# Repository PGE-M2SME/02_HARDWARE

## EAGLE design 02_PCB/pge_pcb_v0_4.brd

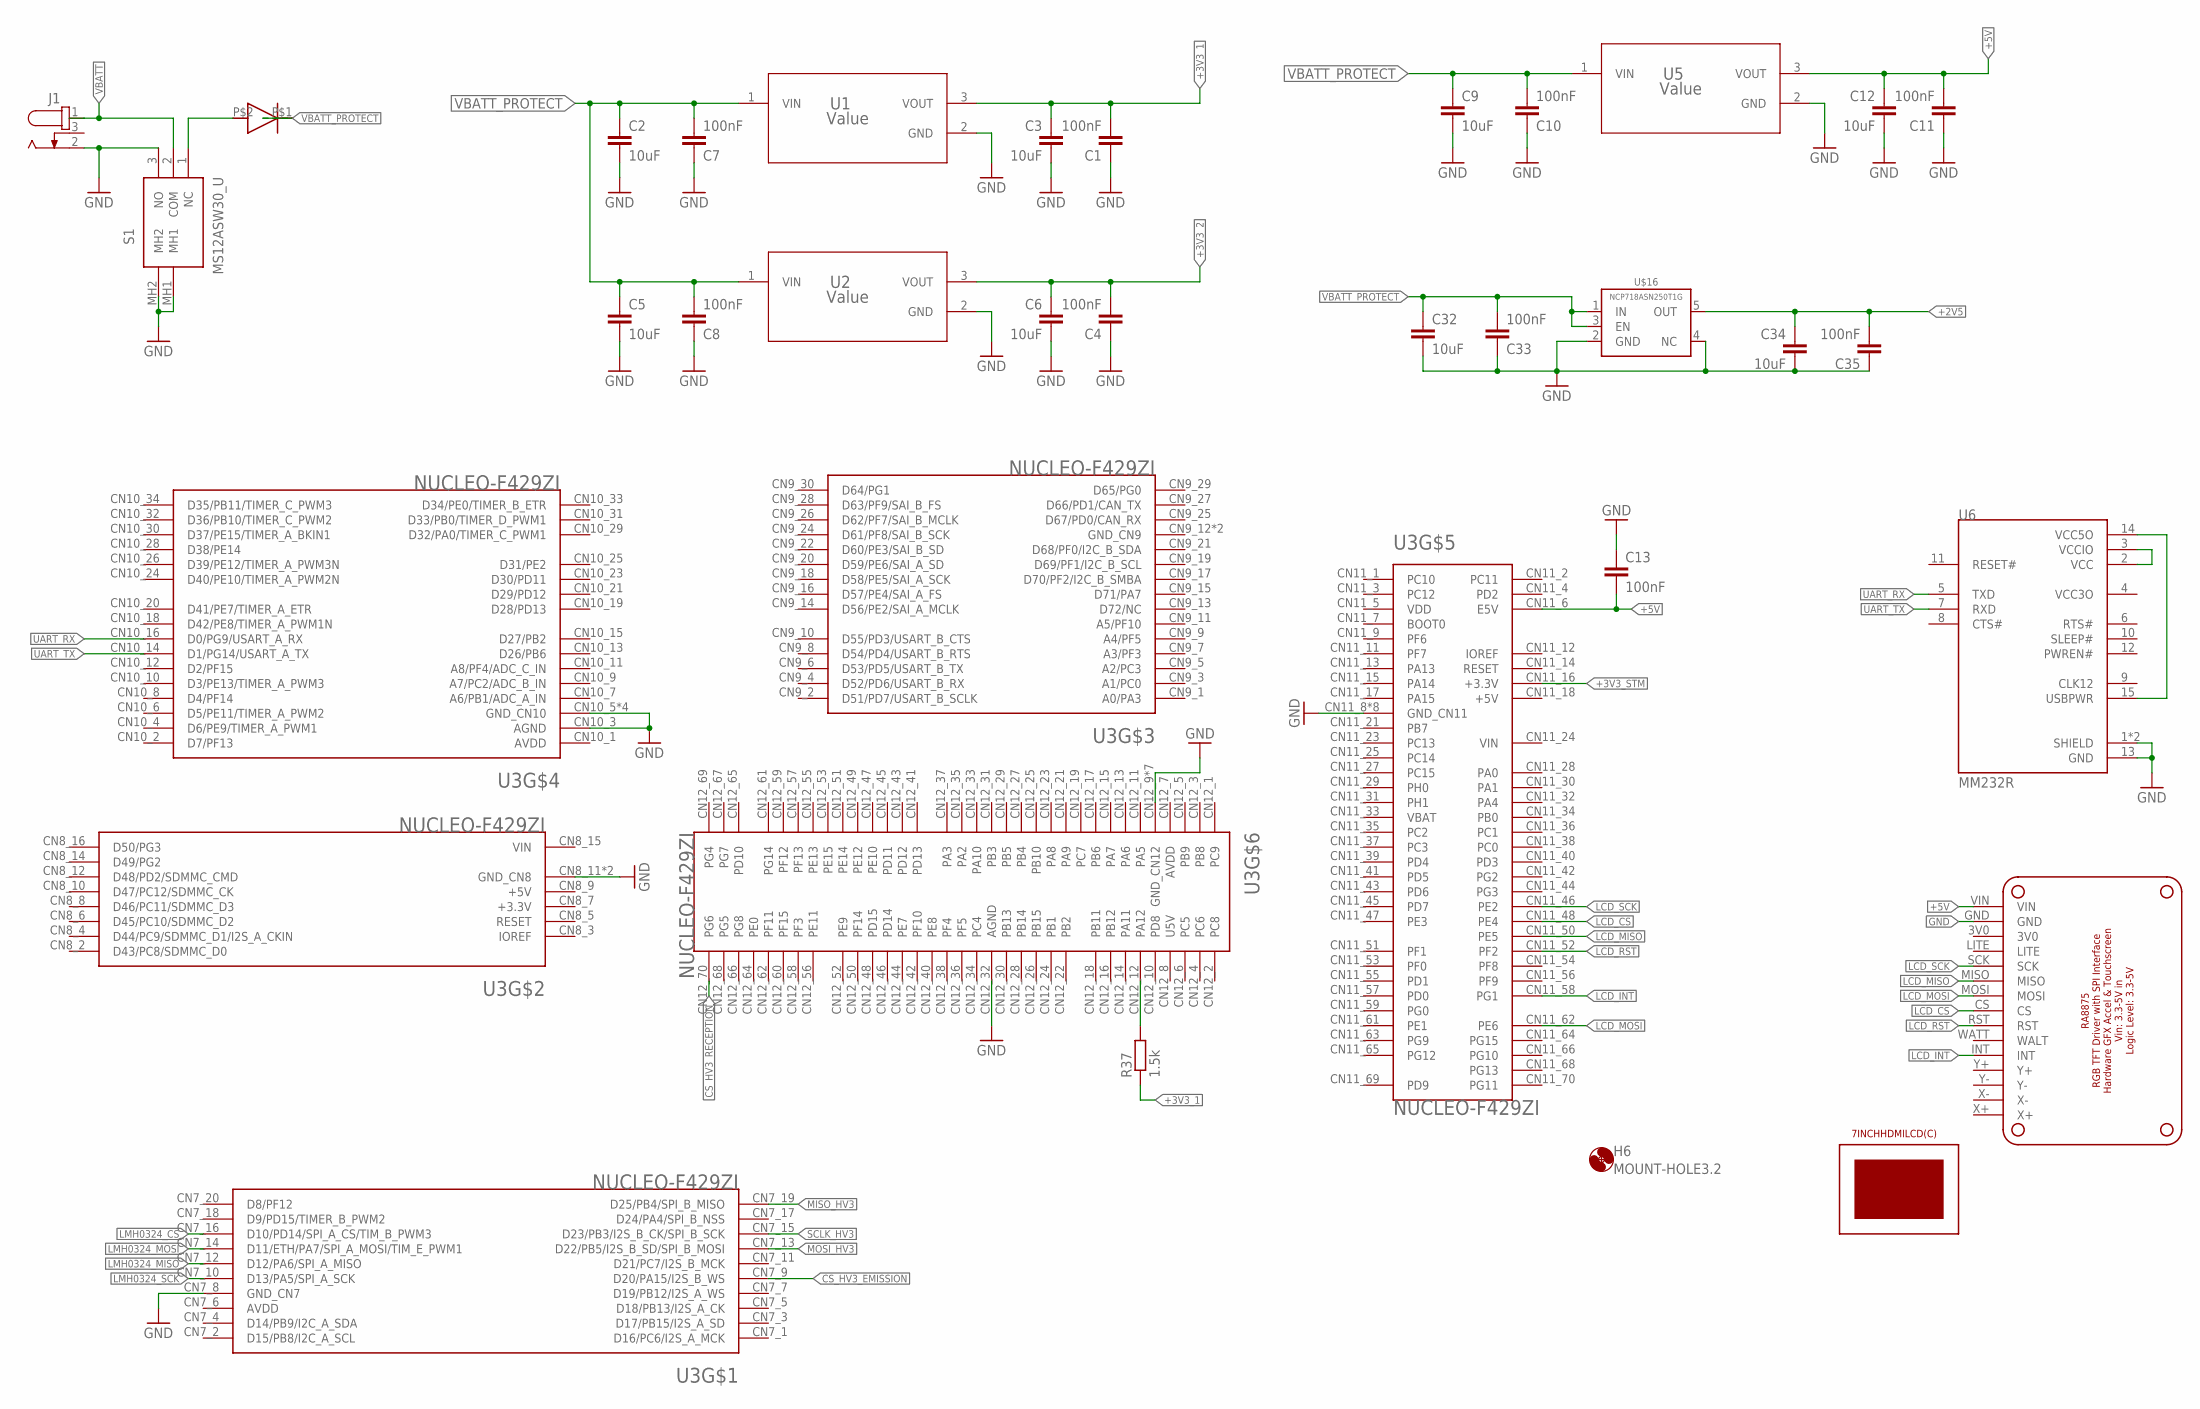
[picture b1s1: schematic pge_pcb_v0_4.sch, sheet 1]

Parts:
C1, C4, C7, C8, C10, C11, C13, C33, C35: 100nF; C0603
C2, C9, C32: 10uF; C0805
C3, C5, C6, C12, C34: 10uF; C0603
H6: MOUNT-HOLE3.2; 3,2
J1: 694106301002
R37: 1.5k; R0603
S1: MS12ASW30_U; MS12ASW30U
U1, U2, U5: Value; EAB0003A
U3: NUCLEO-F429ZI; MODULE_NUCLEO-F429ZI
U6: MM232R; FTDI_MM232R
U$1: V8PAL45HM3_A/I; DO-221BC(SMPA)
U$3: 7INCHHDMILCD(C)
U$15: RA8875_BOARD; RA88758_BOARD
U$16: NCP718ASN250T1G; SOT23-5

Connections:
+2V5: C34.1, C35.2, U$16.5 (OUT); also elsewhere on the board
+3V3_1: C1.2, C3.1, R37.1, U1.3 (VOUT); also elsewhere on the board
+3V3_2: C4.2, C6.1, U2.3 (VOUT); also elsewhere on the board
+3V3_STM: U3.CN11_16 (+3.3V)
+5V: C11.2, C12.1, C13.2, U3.CN11_6 (E5V), U5.3 (VOUT), U$15.VIN; also elsewhere on the board
CS_HV3_EMISSION: U3.CN7_9 (D20/PA15/I2S_B_WS); also elsewhere on the board
CS_HV3_RECEPTION: U3.CN12_70 (PG6); also elsewhere on the board
GND: C1.1, C2.2, C3.2, C4.1, C5.2, C6.2, C7.1, C8.1, C9.2, C10.1, C11.1, C12.2, C13.1, C32.2, C33.1, C34.2, C35.1, J1.2, S1.3 (NO), S1.MH1, S1.MH2, U1.2 (GND), U2.2 (GND), U3.CN7_8 (GND_CN7), U3.CN8_11 (GND_CN8), U3.CN8_13 (GND_CN8), U3.CN10_3 (AGND), U3.CN10_5 (GND_CN10), U3.CN10_17 (GND_CN10), U3.CN10_22 (GND_CN10), U3.CN10_27 (GND_CN10), U3.CN11_8 (GND_CN11), U3.CN11_19 (GND_CN11), U3.CN11_20 (GND_CN11), U3.CN11_22 (GND_CN11), U3.CN11_49 (GND_CN11), U3.CN11_60 (GND_CN11), U3.CN11_71 (GND_CN11), U3.CN11_72 (GND_CN11), U3.CN12_9 (GND_CN12), U3.CN12_20 (GND_CN12), U3.CN12_32 (AGND), U3.CN12_39 (GND_CN12), U3.CN12_54 (GND_CN12), U3.CN12_63 (GND_CN12), U3.CN12_71 (GND_CN12), U3.CN12_72 (GND_CN12), U5.2 (GND), U6.1 (SHIELD), U6.13 (GND), U6.16 (SHIELD), U$15.GND, U$16.2 (GND), U$16.4 (NC); also elsewhere on the board
LCD_CS: U3.CN11_48 (PE4), U$15.CS
LCD_INT: U3.CN11_58 (PG1), U$15.INT
LCD_MISO: U3.CN11_50 (PE5), U$15.MISO
LCD_MOSI: U3.CN11_62 (PE6), U$15.MOSI
LCD_RST: U3.CN11_52 (PF2), U$15.RST
LCD_SCK: U3.CN11_46 (PE2), U$15.SCK
LMH0324_CS: U3.CN7_16 (D10/PD14/SPI_A_CS/TIM_B_PWM3); also elsewhere on the board
LMH0324_MISO: U3.CN7_12 (D12/PA6/SPI_A_MISO); also elsewhere on the board
LMH0324_MOSI: U3.CN7_14 (D11/ETH/PA7/SPI_A_MOSI/TIM_E_PWM1); also elsewhere on the board
LMH0324_SCK: U3.CN7_10 (D13/PA5/SPI_A_SCK); also elsewhere on the board
MISO_HV3: U3.CN7_19 (D25/PB4/SPI_B_MISO); also elsewhere on the board
MOSI_HV3: U3.CN7_13 (D22/PB5/I2S_B_SD/SPI_B_MOSI); also elsewhere on the board
unnamed: S1.1 (NC), U$1.P$2 (ANODE)
unnamed: U6.2 (VCC), U6.3 (VCCIO)
unnamed: U6.14 (VCC5O), U6.15 (USBPWR)
unnamed: R37.2, U3.CN12_12 (PA12)
SCLK_HV3: U3.CN7_15 (D23/PB3/I2S_B_CK/SPI_B_SCK); also elsewhere on the board
UART_RX: U3.CN10_16 (D0/PG9/USART_A_RX), U6.5 (TXD)
UART_TX: U3.CN10_14 (D1/PG14/USART_A_TX), U6.7 (RXD)
VBATT: J1.1, S1.2 (COM)
VBATT_PROTECT: C2.1, C5.1, C7.2, C8.2, C9.1, C10.2, C32.1, C33.2, U1.1 (VIN), U2.1 (VIN), U5.1 (VIN), U$1.P$1 (CATHODE), U$16.1 (IN), U$16.3 (EN)

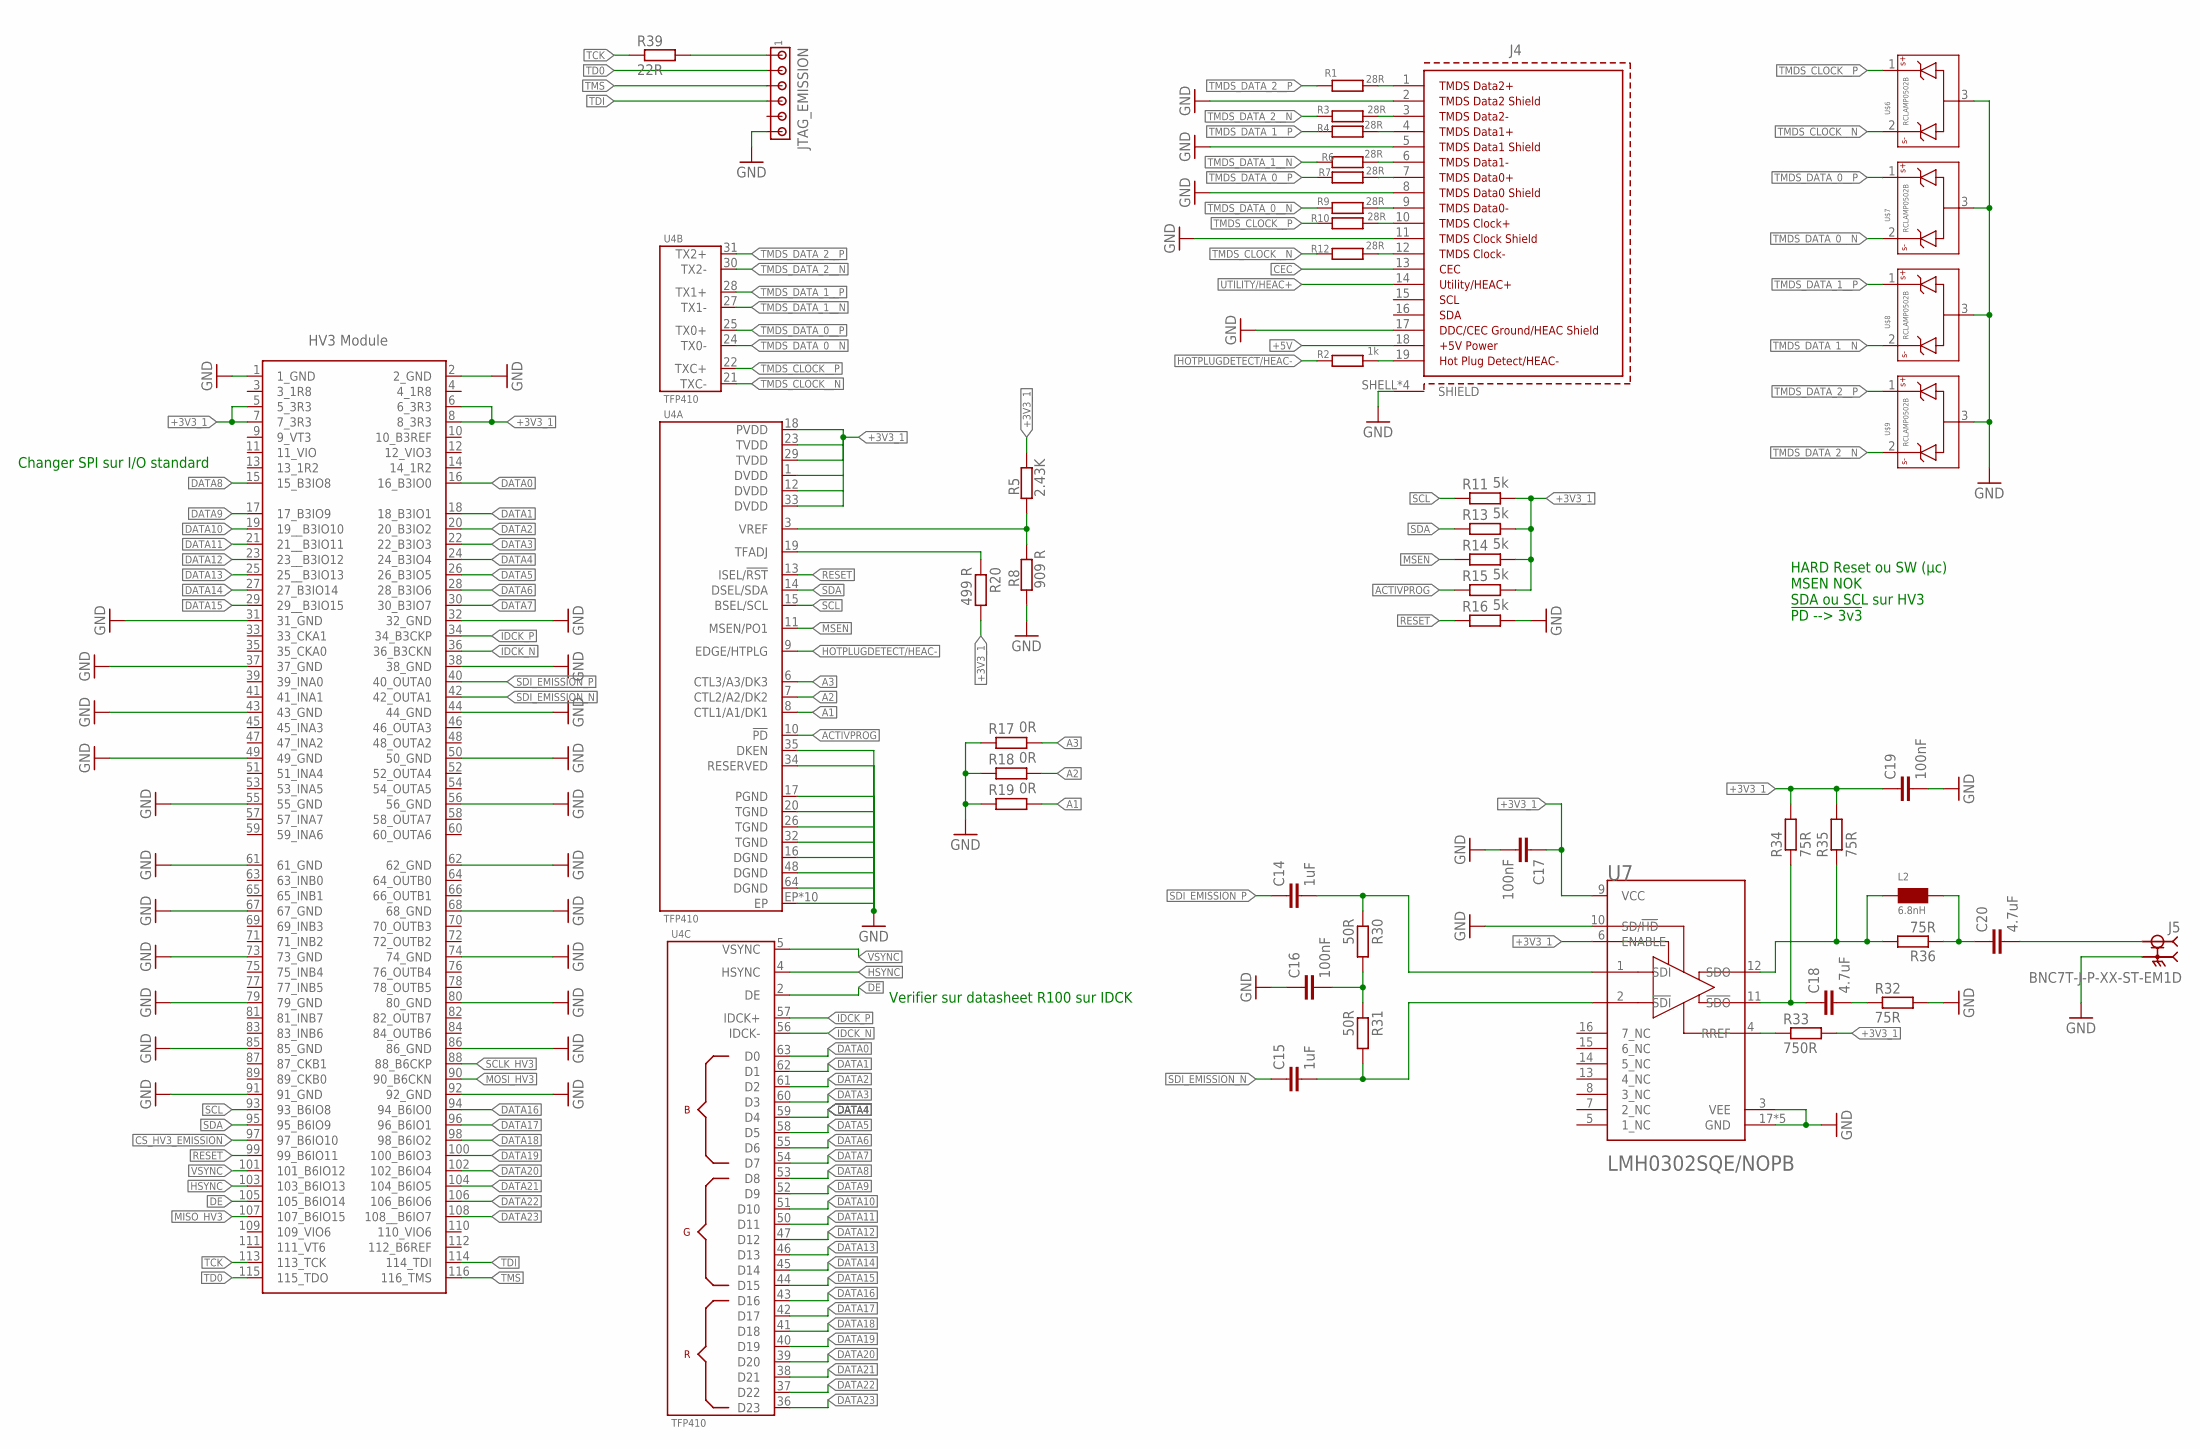
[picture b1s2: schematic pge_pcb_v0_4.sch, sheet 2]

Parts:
C14, C15: 1uF; C0603
C16, C17, C19: 100nF; C0603
C18, C20: 4.7uF; C0603
J4: 685119134923
J5: BNC7T-J-P-XX-ST-EM1D; SAMTEC_BNC7T-J-P-XX-ST-EM1D
JTAG_EMISSION: MTA06-100; 10X06MTA
L2: 6.8nH; L0603
R1, R3, R4, R6, R7, R9, R10, R12: 28R; R0402
R2: 1k; R0603
R5: 2.43K; R0603
R8: 909 R; R0603
R11, R13, R14, R15, R16: 5k; R0603
R17, R18, R19: 0R; R0603
R20: 499 R; R0603
R30, R31: 50R; R0603
R32, R34, R35, R36: 75R; R0402
R33: 750R; R0402
R39: 22R; R0603
U4: TFP410; PQFP-64
U7: TEXAS_INSTRUMENTS_LMH0302SQE-NOPBTEXAS_INSTRUMENT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; TEXAS_INSTRUMENTS_LMH0302SQE-NOPB_0
U$4: MEC1-160-02-L-D-RA1-SL
U$6, U$7, U$8, U$9: RCLAMP0502B; SC75_INFINEON

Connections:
+3V3_1: C17.1, C19.1, R5.2, R11.2, R13.2, R14.2, R15.2, R20.2, R33.2, R34.2, R35.2, U4.1 (DVDD), U4.12 (DVDD), U4.18 (PVDD), U4.23 (TVDD), U4.29 (TVDD), U4.33 (DVDD), U7.6 (ENABLE), U7.9 (VCC), U$4.5 (5_3R3), U$4.6 (6_3R3), U$4.7 (7_3R3), U$4.8 (8_3R3); also elsewhere on the board
+5V: J4.18 (+5VPOWER); also elsewhere on the board
A1: R19.2, U4.8 (CTL1/A1/DK1)
A2: R18.2, U4.7 (CTL2/A2/DK2)
A3: R17.2, U4.6 (CTL3/A3/DK3)
ACTIVPROG: R15.1, U4.10 (!PD)
CEC: J4.13 (CEC)
CS_HV3_EMISSION: U$4.97 (97_B6IO10); also elsewhere on the board
DATA0: U4.63 (D0), U$4.16 (16_B3IO0)
DATA1: U4.62 (D1), U$4.18 (18_B3IO1)
DATA2: U4.61 (D2), U$4.20 (20_B3IO2)
DATA3: U4.60 (D3), U$4.22 (22_B3IO3)
DATA4: U4.59 (D4), U$4.24 (24_B3IO4)
DATA5: U4.58 (D5), U$4.26 (26_B3IO5)
DATA6: U4.55 (D6), U$4.28 (28_B3IO6)
DATA7: U4.54 (D7), U$4.30 (30_B3IO7)
DATA8: U4.53 (D8), U$4.15 (15_B3IO8)
DATA9: U4.52 (D9), U$4.17 (17_B3IO9)
DATA10: U4.51 (D10), U$4.19 (19__B3IO10)
DATA11: U4.50 (D11), U$4.21 (21__B3IO11)
DATA12: U4.47 (D12), U$4.23 (23__B3IO12)
DATA13: U4.46 (D13), U$4.25 (25__B3IO13)
DATA14: U4.45 (D14), U$4.27 (27_B3IO14)
DATA15: U4.44 (D15), U$4.29 (29__B3IO15)
DATA16: U4.43 (D16), U$4.94 (94_B6IO0)
DATA17: U4.42 (D17), U$4.96 (96_B6IO1)
DATA18: U4.41 (D18), U$4.98 (98_B6IO2)
DATA19: U4.40 (D19), U$4.100 (100_B6IO3)
DATA20: U4.39 (D20), U$4.102 (102_B6IO4)
DATA21: U4.38 (D21), U$4.104 (104_B6IO5)
DATA22: U4.37 (D22), U$4.106 (106_B6IO6)
DATA23: U4.36 (D23), U$4.108 (108__B6IO7)
DE: U4.2 (DE), U$4.105 (105_B6IO14)
GND: C16.1, C17.2, C19.2, J4.2 (TMDSDATA2SHIELD), J4.5 (TMDSDATA1SHIELD), J4.8 (TMDSDATA0SHIELD), J4.11 (TMDSCLOCKSHIELD), J4.17 (DDC/CEC/HECGROUND), J4.SHELL (SHIELD), J4.SHELL1 (SHIELD), J4.SHELL2 (SHIELD), J4.SHELL3 (SHIELD), J5.P$1 (2), J5.P$2 (2), J5.P$3 (2), J5.P$4 (2), J5.P$5 (2), J5.P$6 (2), J5.P$7 (2), J5.P$8 (2), J5.P$9 (2), J5.P$10 (2), J5.S1 (2), J5.S2 (2), J5.S3 (2), J5.S4 (2), JTAG_EMISSION.6, R8.1, R16.2, R17.1, R18.1, R19.1, R32.2, U4.16 (DGND), U4.17 (PGND), U4.20 (TGND), U4.26 (TGND), U4.32 (TGND), U4.34 (RESERVED), U4.35 (DKEN), U4.48 (DGND), U4.64 (DGND), U4.EP, U4.P$1 (EP), U4.P$2 (EP), U4.P$3 (EP), U4.P$4 (EP), U4.P$5 (EP), U4.P$6 (EP), U4.P$7 (EP), U4.P$8 (EP), U4.P$9 (EP), U7.3 (VEE), U7.10 (SD/!HD!), U7.17 (GND), U7.P$1 (GND), U7.P$2 (GND), U7.P$3 (GND), U7.P$4 (GND), U$4.1 (1_GND), U$4.2 (2_GND), U$4.31 (31_GND), U$4.32 (32_GND), U$4.37 (37_GND), U$4.38 (38_GND), U$4.43 (43_GND), U$4.44 (44_GND), U$4.49 (49_GND), U$4.50 (50_GND), U$4.55 (55_GND), U$4.56 (56_GND), U$4.61 (61_GND), U$4.62 (62_GND), U$4.67 (67_GND), U$4.68 (68_GND), U$4.73 (73_GND), U$4.74 (74_GND), U$4.79 (79_GND), U$4.80 (80_GND), U$4.85 (85_GND), U$4.86 (86_GND), U$4.91 (91_GND), U$4.92 (92_GND), U$6.3, U$7.3, U$8.3, U$9.3; also elsewhere on the board
HOTPLUGDETECT/HEAC-: R2.1, U4.9 (EDGE/HTPLG)
HSYNC: U4.4 (HSYNC), U$4.103 (103_B6IO13)
IDCK_N: U4.56 (IDCK-), U$4.36 (36_B3CKN)
IDCK_P: U4.57 (IDCK+), U$4.34 (34_B3CKP)
MISO_HV3: U$4.107 (107_B6IO15); also elsewhere on the board
MOSI_HV3: U$4.90 (90_B6CKN); also elsewhere on the board
MSEN: R14.1, U4.11 (MSEN/PO1)
unnamed: JTAG_EMISSION.1, R39.2
unnamed: J4.19 (HOTPLUGDETECT/HEAC-), R2.2
unnamed: R20.1, U4.19 (TFADJ)
unnamed: R5.1, R8.2, U4.3 (VREF)
unnamed: C14.2, R30.1, U7.1 (SDI)
unnamed: C16.2, R30.2, R31.1
unnamed: R33.1, U7.4 (RREF)
unnamed: C15.2, R31.2, U7.2 (!SDI!)
unnamed: C18.1, R34.1, U7.11 (!SDO!)
unnamed: C18.2, R32.1
unnamed: L2.1, R35.1, R36.2, U7.12 (SDO)
unnamed: C20.2, J5.1
unnamed: C20.1, L2.2, R36.1
RESET: R16.1, U4.13 (ISEL/!RST), U$4.99 (99_B6IO11)
SCL: R11.1, U4.15 (BSEL/SCL), U$4.93 (93_B6IO8)
SCLK_HV3: U$4.88 (88_B6CKP); also elsewhere on the board
SDA: R13.1, U4.14 (DSEL/SDA), U$4.95 (95_B6IO9)
SDI_EMISSION_N: C15.1, U$4.42 (42_OUTA1)
SDI_EMISSION_P: C14.1, U$4.40 (40_OUTA0)
TCK: R39.1, U$4.113 (113_TCK)
TD0: JTAG_EMISSION.2, U$4.115 (115_TDO)
TDI: JTAG_EMISSION.4, U$4.114 (114_TDI)
TMDS_CLK_N: J4.12 (TMDSCLOCK-), R12.2
TMDS_CLK_P: J4.10 (TMDSCLOCK+), R10.2
TMDS_CLOCK__N: R12.1, U4.21 (TXC-), U$6.2
TMDS_CLOCK__P: R10.1, U4.22 (TXC+), U$6.1
TMDS_DATA_0_N: J4.9 (TMDSDATA0-), R9.2
TMDS_DATA_0_P: J4.7 (TMDSDATA0+), R7.2
TMDS_DATA_0__N: R9.1, U4.24 (TX0-), U$7.2
TMDS_DATA_0__P: R7.1, U4.25 (TX0+), U$7.1
TMDS_DATA_1_N: J4.6 (TMDSDATA1-), R6.2
TMDS_DATA_1_P: J4.4 (TMDSDATA1+), R4.2
TMDS_DATA_1__N: R6.1, U4.27 (TX1-), U$8.2
TMDS_DATA_1__P: R4.1, U4.28 (TX1+), U$8.1
TMDS_DATA_2_N: J4.1 (TMDSDATA2+), R1.2
TMDS_DATA_2_P: J4.3 (TMDSDATA2-), R3.2
TMDS_DATA_2__N: R3.1, U4.30 (TX2-), U$9.2
TMDS_DATA_2__P: R1.1, U4.31 (TX2+), U$9.1
TMS: JTAG_EMISSION.3, U$4.116 (116_TMS)
UTILITY/HEAC+: J4.14 (UTILITY/HEAC+)
VSYNC: U4.5 (VSYNC), U$4.101 (101_B6IO12)

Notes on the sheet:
HARD Reset ou SW (µc) MSEN NOK SDA ou SCL sur HV3 !PD --> 3v3
Verifier sur datasheet R100 sur IDCK
Changer SPI sur I/O standard

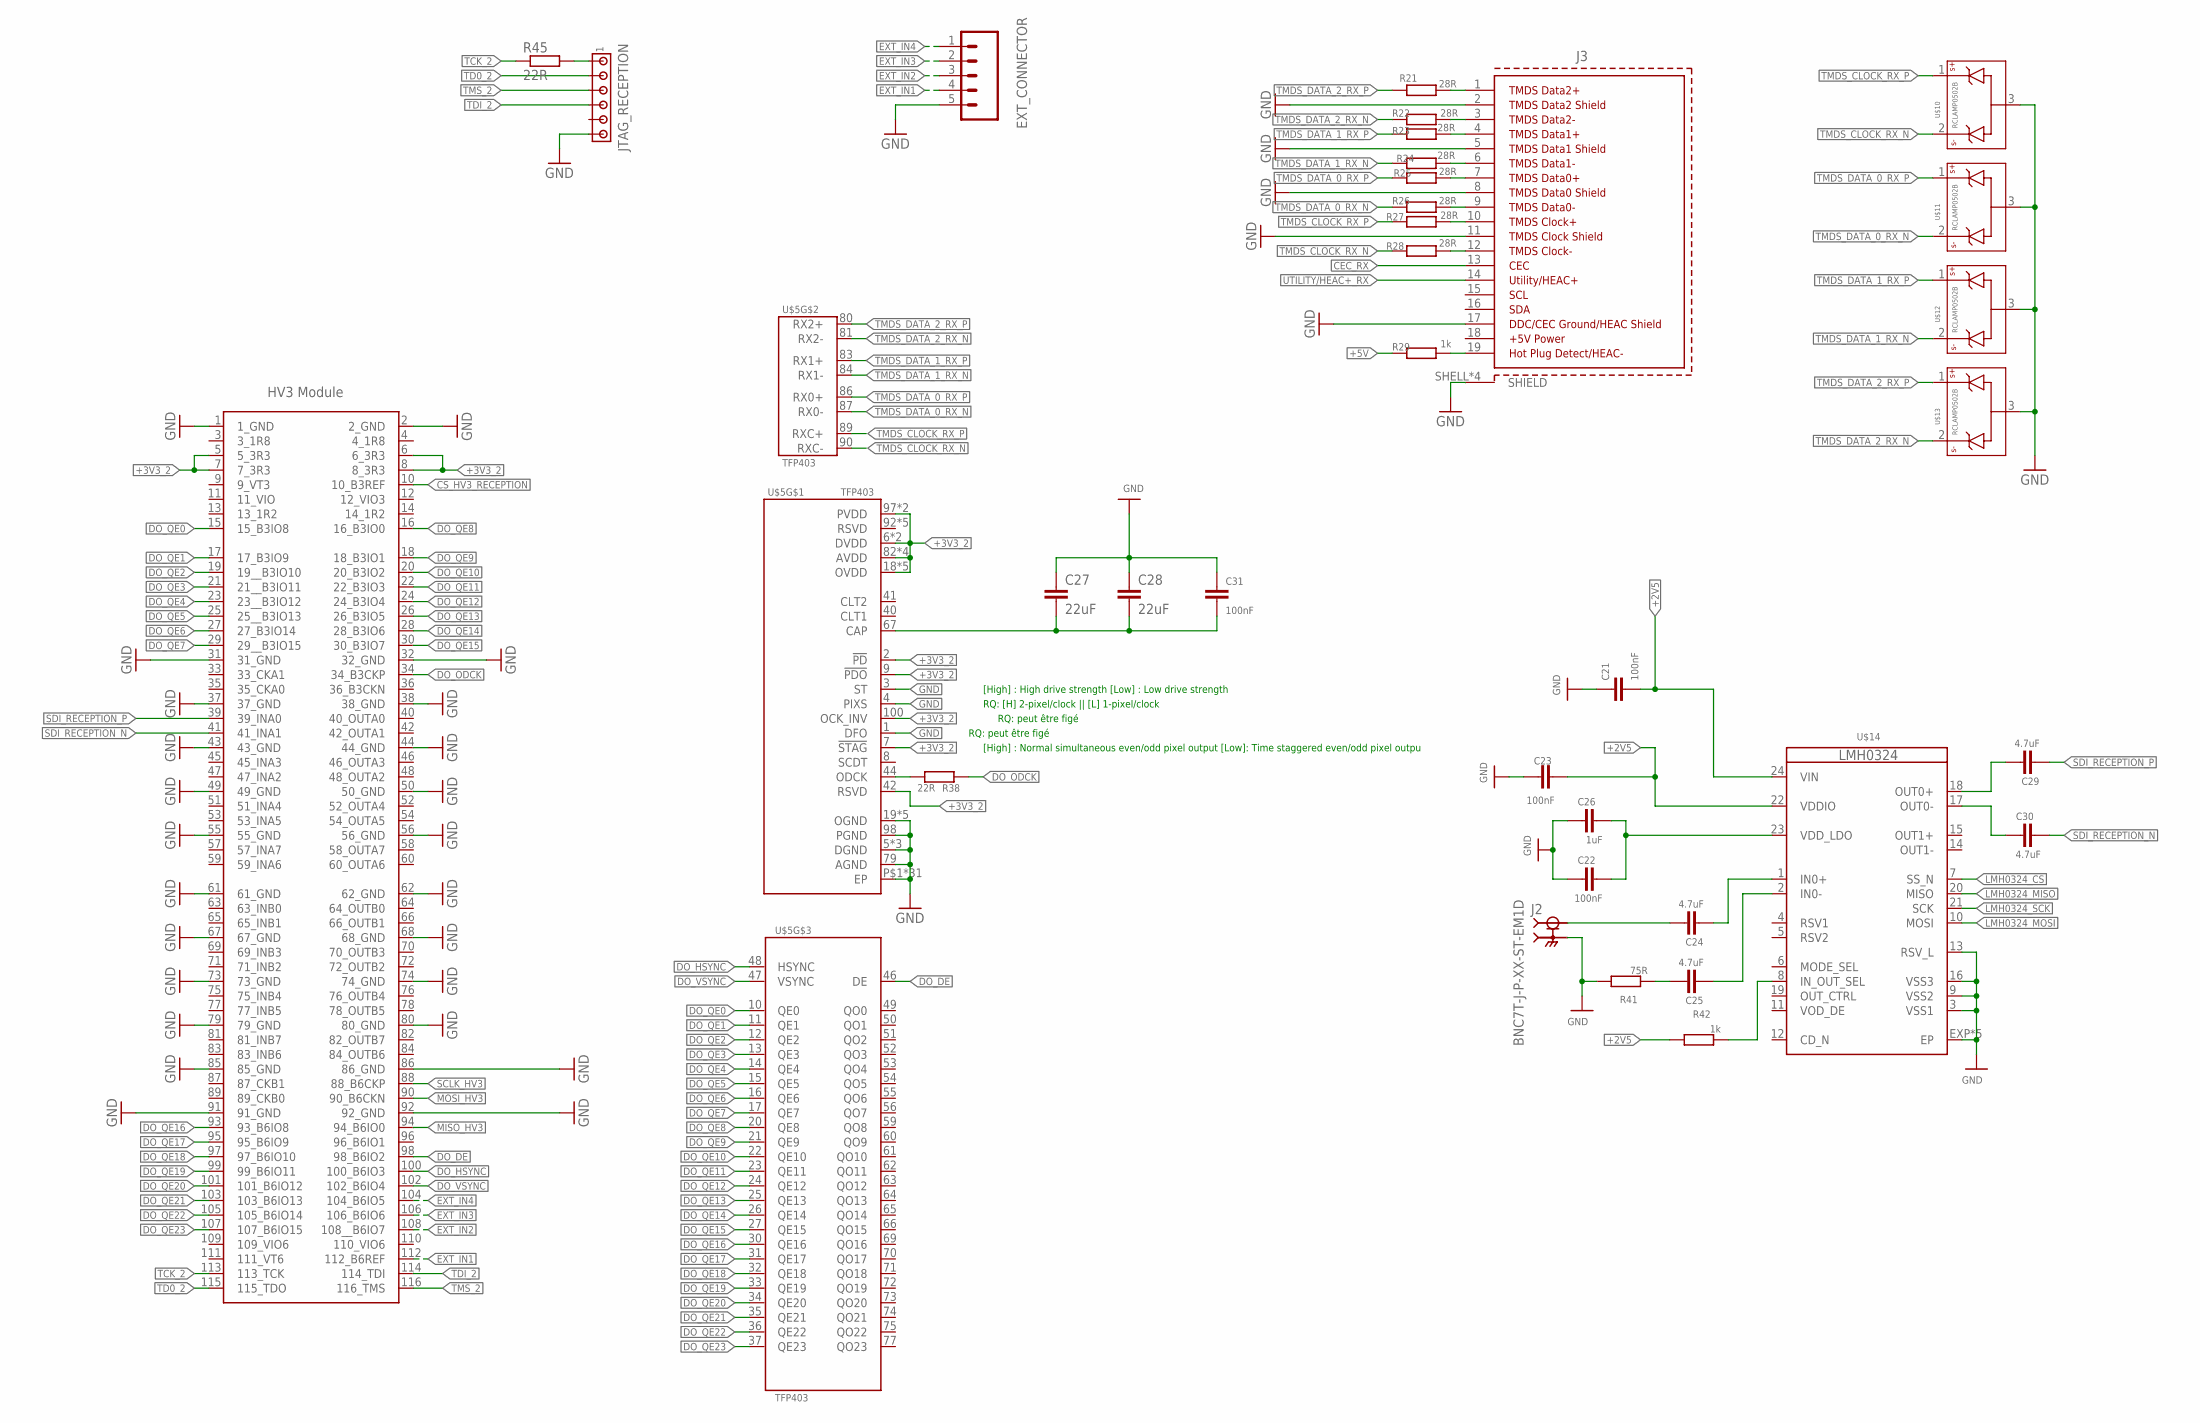
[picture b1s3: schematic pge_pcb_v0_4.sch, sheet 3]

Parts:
C21, C22, C23, C31: 100nF; C0603
C24, C25, C29, C30: 4.7uF; C0603
C26: 1uF; C0603
C27, C28: 22uF; C0805K
EXT_CONNECTOR: M05; 05P
J2: BNC7T-J-P-XX-ST-EM1D; SAMTEC_BNC7T-J-P-XX-ST-EM1D
J3: 685119134923
JTAG_RECEPTION: MTA06-100; 10X06MTA
R21, R22, R23, R24, R25, R26, R27, R28: 28R; R0402
R29, R42: 1k; R0603
R38, R45: 22R; R0603
R41: 75R; R0603
U$2: MEC1-160-02-L-D-RA1-SL
U$5: TFP403; PQFP100
U$10, U$11, U$12, U$13: RCLAMP0502B; SC75_INFINEON
U$14: LMH0324; QFN24-4X4

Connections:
+2V5: C21.2, C23.1, R42.1, U$14.22 (VDDIO), U$14.24 (VIN); also elsewhere on the board
+3V3_2: U$2.5 (5_3R3), U$2.6 (6_3R3), U$2.7 (7_3R3), U$2.8 (8_3R3), U$5.2 (!PD), U$5.6 (DVDD), U$5.7 (!STAG), U$5.9 (!PDO), U$5.18 (OVDD), U$5.29 (OVDD), U$5.38 (DVDD), U$5.42 (RSVD), U$5.43 (OVDD), U$5.57 (OVDD), U$5.78 (OVDD), U$5.82 (AVDD), U$5.85 (AVDD), U$5.88 (AVDD), U$5.91 (AVDD), U$5.97 (PVDD), U$5.99 (PVDD), U$5.100 (OCK_INV); also elsewhere on the board
+5V: R29.1; also elsewhere on the board
+5VPOWER: J3.18 (+5VPOWER)
CEC_RX: J3.13 (CEC)
CS_HV3_RECEPTION: U$2.10 (10_B3REF); also elsewhere on the board
DO_DE: U$2.98 (98_B6IO2), U$5.46 (DE)
DO_HSYNC: U$2.100 (100_B6IO3), U$5.48 (HSYNC)
DO_ODCK: R38.1, U$2.34 (34_B3CKP)
DO_QE0: U$2.15 (15_B3IO8), U$5.10 (QE0)
DO_QE1: U$2.17 (17_B3IO9), U$5.11 (QE1)
DO_QE2: U$2.19 (19__B3IO10), U$5.12 (QE2)
DO_QE3: U$2.21 (21__B3IO11), U$5.13 (QE3)
DO_QE4: U$2.23 (23__B3IO12), U$5.14 (QE4)
DO_QE5: U$2.25 (25__B3IO13), U$5.15 (QE5)
DO_QE6: U$2.27 (27_B3IO14), U$5.16 (QE6)
DO_QE7: U$2.29 (29__B3IO15), U$5.17 (QE7)
DO_QE8: U$2.16 (16_B3IO0), U$5.20 (QE8)
DO_QE9: U$2.18 (18_B3IO1), U$5.21 (QE9)
DO_QE10: U$2.20 (20_B3IO2), U$5.22 (QE10)
DO_QE11: U$2.22 (22_B3IO3), U$5.23 (QE11)
DO_QE12: U$2.24 (24_B3IO4), U$5.24 (QE12)
DO_QE13: U$2.26 (26_B3IO5), U$5.25 (QE13)
DO_QE14: U$2.28 (28_B3IO6), U$5.26 (QE14)
DO_QE15: U$2.30 (30_B3IO7), U$5.27 (QE15)
DO_QE16: U$2.93 (93_B6IO8), U$5.30 (QE16)
DO_QE17: U$2.95 (95_B6IO9), U$5.31 (QE17)
DO_QE18: U$2.97 (97_B6IO10), U$5.32 (QE18)
DO_QE19: U$2.99 (99_B6IO11), U$5.33 (QE19)
DO_QE20: U$2.101 (101_B6IO12), U$5.34 (QE20)
DO_QE21: U$2.103 (103_B6IO13), U$5.35 (QE21)
DO_QE22: U$2.105 (105_B6IO14), U$5.36 (QE22)
DO_QE23: U$2.107 (107_B6IO15), U$5.37 (QE23)
DO_VSYNC: U$2.102 (102_B6IO4), U$5.47 (VSYNC)
EXT_IN1: EXT_CONNECTOR.4, U$2.112 (112_B6REF)
EXT_IN2: EXT_CONNECTOR.3, U$2.108 (108__B6IO7)
EXT_IN3: EXT_CONNECTOR.2, U$2.106 (106_B6IO6)
EXT_IN4: EXT_CONNECTOR.1, U$2.104 (104_B6IO5)
GND: C21.1, C22.2, C23.2, C26.2, C27.1, C28.1, C31.1, EXT_CONNECTOR.5, J2.P$1 (2), J2.P$2 (2), J2.P$3 (2), J2.P$4 (2), J2.P$5 (2), J2.P$6 (2), J2.P$7 (2), J2.P$8 (2), J2.P$9 (2), J2.P$10 (2), J2.S1 (2), J2.S2 (2), J2.S3 (2), J2.S4 (2), J3.2 (TMDSDATA2SHIELD), J3.5 (TMDSDATA1SHIELD), J3.8 (TMDSDATA0SHIELD), J3.11 (TMDSCLOCKSHIELD), J3.17 (DDC/CEC/HECGROUND), J3.SHELL (SHIELD), J3.SHELL1 (SHIELD), J3.SHELL2 (SHIELD), J3.SHELL3 (SHIELD), JTAG_RECEPTION.6, R41.1, U$2.1 (1_GND), U$2.2 (2_GND), U$2.31 (31_GND), U$2.32 (32_GND), U$2.37 (37_GND), U$2.38 (38_GND), U$2.43 (43_GND), U$2.44 (44_GND), U$2.49 (49_GND), U$2.50 (50_GND), U$2.55 (55_GND), U$2.56 (56_GND), U$2.61 (61_GND), U$2.62 (62_GND), U$2.67 (67_GND), U$2.68 (68_GND), U$2.73 (73_GND), U$2.74 (74_GND), U$2.79 (79_GND), U$2.80 (80_GND), U$2.85 (85_GND), U$2.86 (86_GND), U$2.91 (91_GND), U$2.92 (92_GND), U$5.1 (DFO), U$5.3 (ST), U$5.4 (PIXS), U$5.5 (DGND), U$5.19 (OGND), U$5.28 (OGND), U$5.39 (DGND), U$5.45 (OGND), U$5.58 (OGND), U$5.68 (DGND), U$5.76 (OGND), U$5.79 (AGND), U$5.98 (PGND), U$5.P$1 (EP), U$5.P$2 (EP), U$5.P$3 (EP), U$5.P$4 (EP), U$5.P$5 (EP), U$5.P$6 (EP), U$5.P$7 (EP), U$5.P$14 (EP), U$5.P$15 (EP), U$5.P$16 (EP), U$5.P$17 (EP), U$5.P$18 (EP), U$5.P$19 (EP), U$5.P$20 (EP), U$5.P$21 (EP), U$5.P$22 (EP), U$5.P$23 (EP), U$5.P$24 (EP), U$5.P$25 (EP), U$5.P$26 (EP), U$5.P$27 (EP), U$5.P$28 (EP), U$5.P$29 (EP), U$5.P$30 (EP), U$5.P$31 (EP), U$5.P$32 (EP), U$5.P$33 (EP), U$5.P$34 (EP), U$5.P$35 (EP), U$5.P$36 (EP), U$5.P$37 (EP), U$10.3, U$11.3, U$12.3, U$13.3, U$14.3 (VSS1), U$14.9 (VSS2), U$14.13 (RSV_L), U$14.16 (VSS3), U$14.EXP (EP), U$14.P$1 (EP), U$14.P$2 (EP), U$14.P$3 (EP), U$14.P$4 (EP); also elsewhere on the board
IN0_N: C25.2, U$14.2 (IN0-)
IN0_P: C24.2, U$14.1 (IN0+)
LMH0324_CS: U$14.7 (SS_N); also elsewhere on the board
LMH0324_MISO: U$14.20 (MISO); also elsewhere on the board
LMH0324_MOSI: U$14.10 (MOSI); also elsewhere on the board
LMH0324_SCK: U$14.21 (SCK); also elsewhere on the board
MISO_HV3: U$2.94 (94_B6IO0); also elsewhere on the board
MOSI_HV3: U$2.90 (90_B6CKN); also elsewhere on the board
unnamed: R42.2, U$14.8 (IN_OUT_SEL)
unnamed: C24.1, J2.1
unnamed: C25.1, R41.2
unnamed: C22.1, C26.1, U$14.23 (VDD_LDO)
unnamed: C27.2, C28.2, C31.2, U$5.67 (CAP)
unnamed: JTAG_RECEPTION.1, R45.2
unnamed: J3.19 (HOTPLUGDETECT/HEAC-), R29.2
unnamed: R38.2, U$5.44 (ODCK)
SCLK_HV3: U$2.88 (88_B6CKP); also elsewhere on the board
SDI_RECEPTION_N: C30.1, U$2.41 (41_INA1)
SDI_RECEPTION_P: C29.2, U$2.39 (39_INA0)
SDI_RECEPTION__N: C30.2, U$14.17 (OUT0-)
SDI_RECEPTION__P: C29.1, U$14.18 (OUT0+)
TCK_2: R45.1, U$2.113 (113_TCK)
TD0_2: JTAG_RECEPTION.2, U$2.115 (115_TDO)
TDI_2: JTAG_RECEPTION.4, U$2.114 (114_TDI)
TMDS_CLOCK_RX_N: R28.1, U$5.90 (RXC-), U$10.2
TMDS_CLOCK_RX_P: R27.1, U$5.89 (RXC+), U$10.1
TMDS_CLOCK_RX__N: J3.10 (TMDSCLOCK+), R27.2
TMDS_CLOCK_RX__P: J3.12 (TMDSCLOCK-), R28.2
TMDS_DATA_0_RX_N: R26.1, U$5.87 (RX0-), U$11.2
TMDS_DATA_0_RX_P: R25.1, U$5.86 (RX0+), U$11.1
TMDS_DATA_0_RX__N: J3.7 (TMDSDATA0+), R25.2
TMDS_DATA_0_RX__P: J3.9 (TMDSDATA0-), R26.2
TMDS_DATA_1_RX_N: R24.1, U$5.84 (RX1-), U$12.2
TMDS_DATA_1_RX_P: R23.1, U$5.83 (RX1+), U$12.1
TMDS_DATA_1_RX__N: J3.4 (TMDSDATA1+), R23.2
TMDS_DATA_1_RX__P: J3.6 (TMDSDATA1-), R24.2
TMDS_DATA_2_RX_N: R22.1, U$5.81 (RX2-), U$13.2
TMDS_DATA_2_RX_P: R21.1, U$5.80 (RX2+), U$13.1
TMDS_DATA_2_RX__N: J3.1 (TMDSDATA2+), R21.2
TMDS_DATA_2_RX__P: J3.3 (TMDSDATA2-), R22.2
TMS_2: JTAG_RECEPTION.3, U$2.116 (116_TMS)
UTILITY/HEAC+_RX: J3.14 (UTILITY/HEAC+)

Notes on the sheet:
RQ: peut être figé
RQ: [H] 2-pixel/clock || [L] 1-pixel/clock
[High] : High drive strength [Low] : Low drive strength
[High] : Normal simultaneous even/odd pixel output [Low]: Time staggered even/odd pixel outpu

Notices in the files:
parts and their libraries:
694106301002_Eagle_WR-DC_rev19a: Copyright: Würth Elektronik
